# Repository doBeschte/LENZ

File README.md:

# LENZ
This is my macropad. I made it for gaming. The macropad includes 11 keys.

The PCB fits into the case.

These are the parts for the case. I rounded all of the visible corners.

I tried to design the wiring diagram clearly.

I have put all of the connections onto one side of the PCB.

# BOM:

1x XIAO RP2040

11x Cherry MX Switches

11x Blank DSA Keycaps

4x M3x16 Bolt

4x M3 Heatset

## completed device

This picture shows the mounted device again. As you can see, it works like it is supposed to.

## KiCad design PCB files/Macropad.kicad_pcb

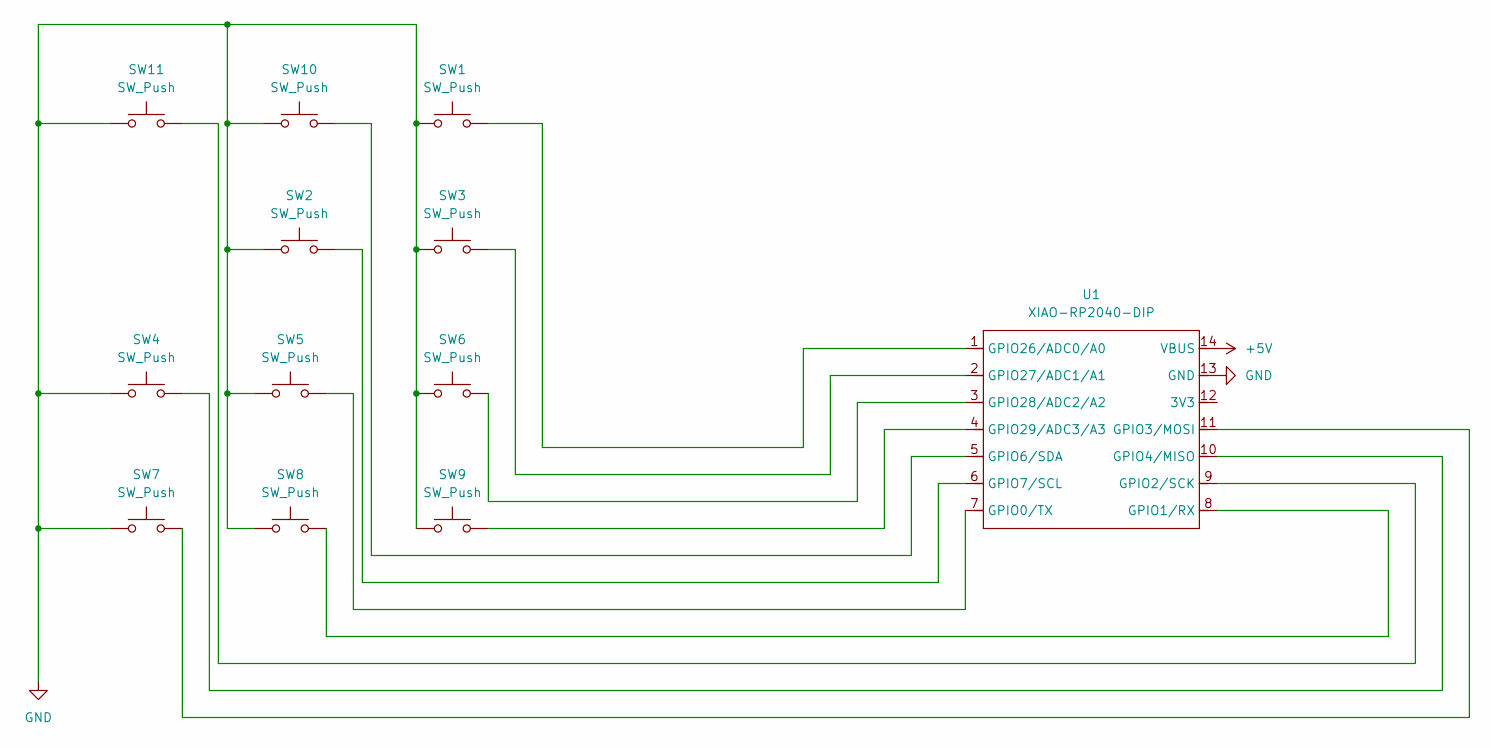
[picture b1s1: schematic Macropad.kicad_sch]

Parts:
SW1, SW2, SW3, SW4, SW5, SW6, SW7, SW8, SW9, SW10, SW11: SW_Push; SW_Cherry_MX_1.00u_PCB
U1: XIAO-RP2040-DIP

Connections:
+5V: U1.14 (VBUS)
GND: SW1.1, SW2.1, SW3.1, SW4.1, SW5.1, SW6.1, SW7.1, SW8.1, SW9.1, SW10.1, SW11.1, U1.13 (GND)
unnamed: SW5.2, U1.7 (GPIO0/TX)
unnamed: SW8.2, U1.8 (GPIO1/RX)
unnamed: SW11.2, U1.9 (GPIO2/SCK)
unnamed: SW7.2, U1.11 (GPIO3/MOSI)
unnamed: SW4.2, U1.10 (GPIO4/MISO)
unnamed: SW10.2, U1.5 (GPIO6/SDA)
unnamed: SW2.2, U1.6 (GPIO7/SCL)
unnamed: SW1.2, U1.1 (GPIO26/ADC0/A0)
unnamed: SW3.2, U1.2 (GPIO27/ADC1/A1)
unnamed: SW6.2, U1.3 (GPIO28/ADC2/A2)
unnamed: SW9.2, U1.4 (GPIO29/ADC3/A3)

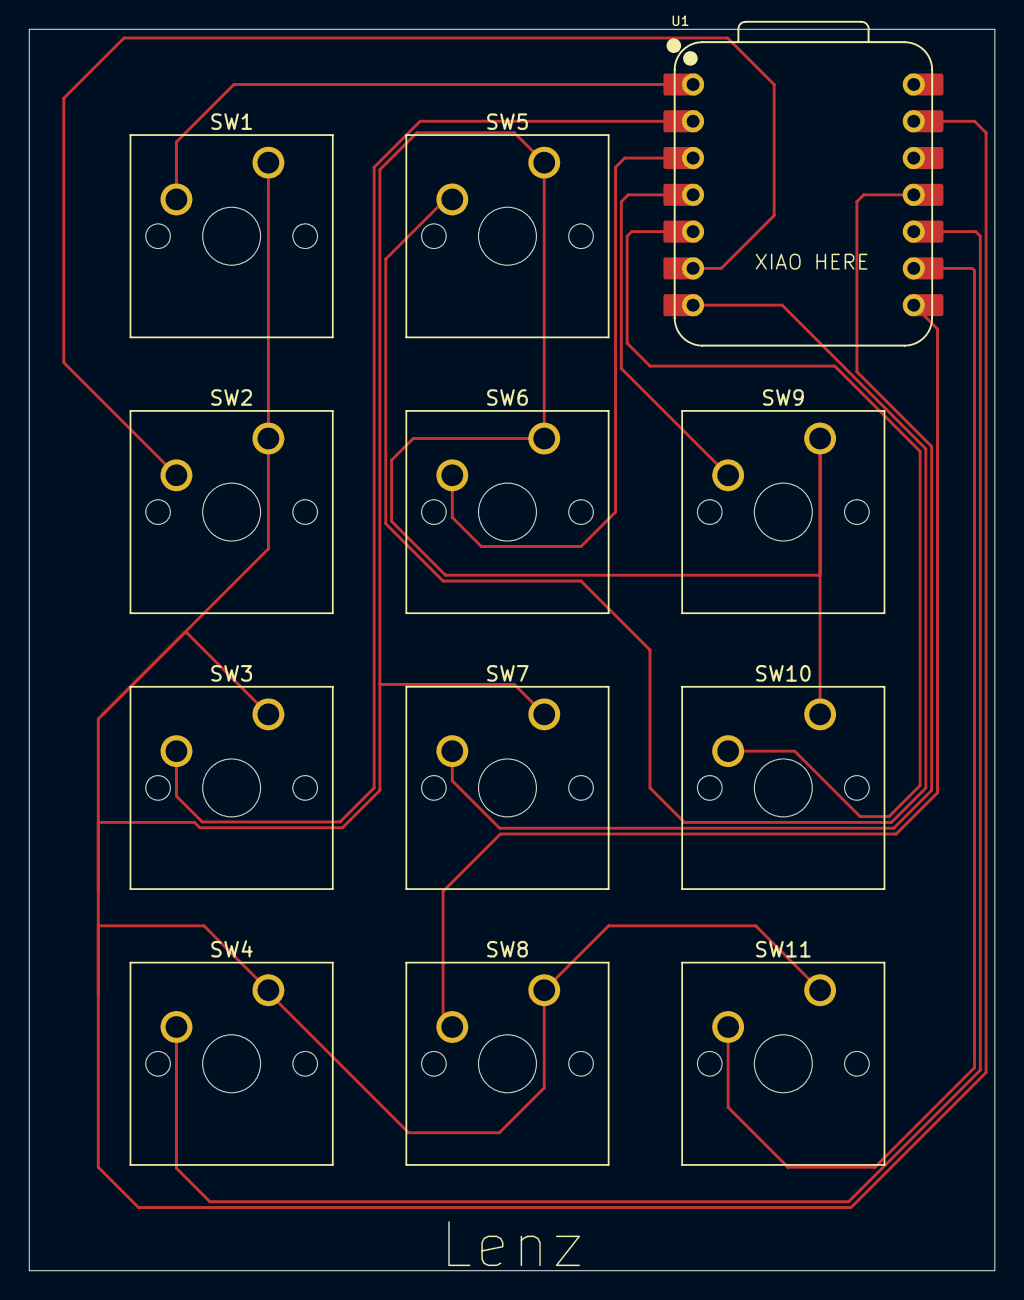
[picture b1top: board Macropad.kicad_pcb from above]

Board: 2 copper layers, 66.7 x 85.7 mm, 12 parts (0 on the bottom side), 12 nets.

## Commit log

2025-12-16 README
    Added detailed description of the LENZ macropad, including images and BOM.
2025-12-16 Update README with images and project information
    Added images and updated project details in README.
2025-12-19 Revise README with macropad details and BOM
    Updated description of the macropad and added information about the PCB fitting into the case.
2026-01-23 Revise README for grammar and add images
    Updated grammar and added images for clarity.
